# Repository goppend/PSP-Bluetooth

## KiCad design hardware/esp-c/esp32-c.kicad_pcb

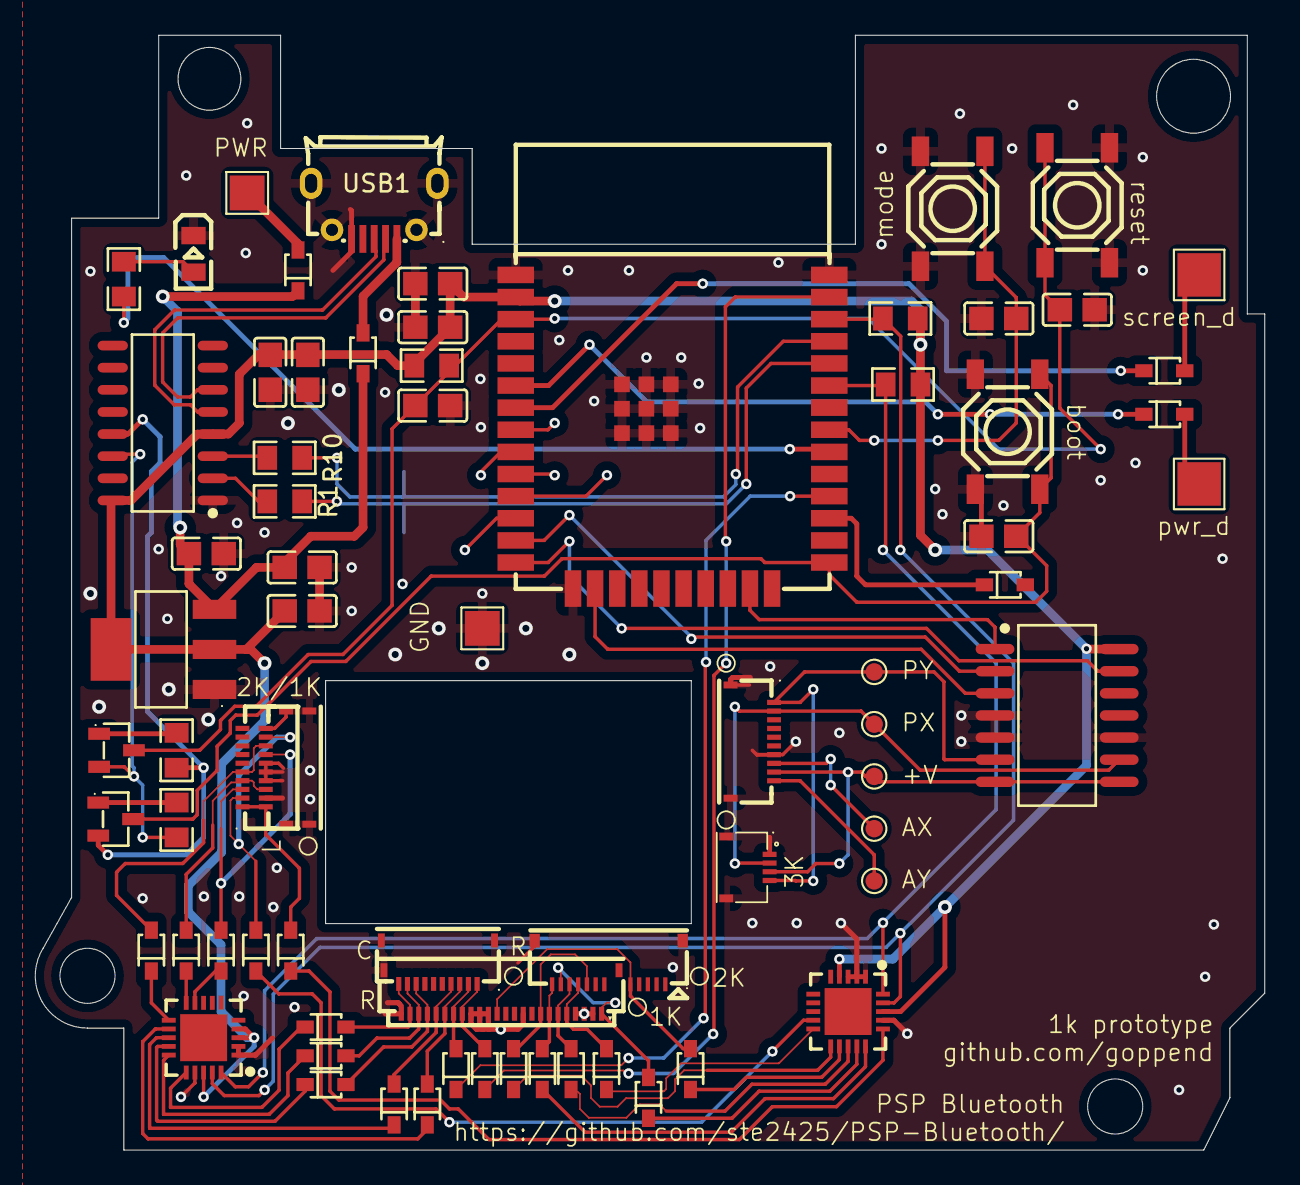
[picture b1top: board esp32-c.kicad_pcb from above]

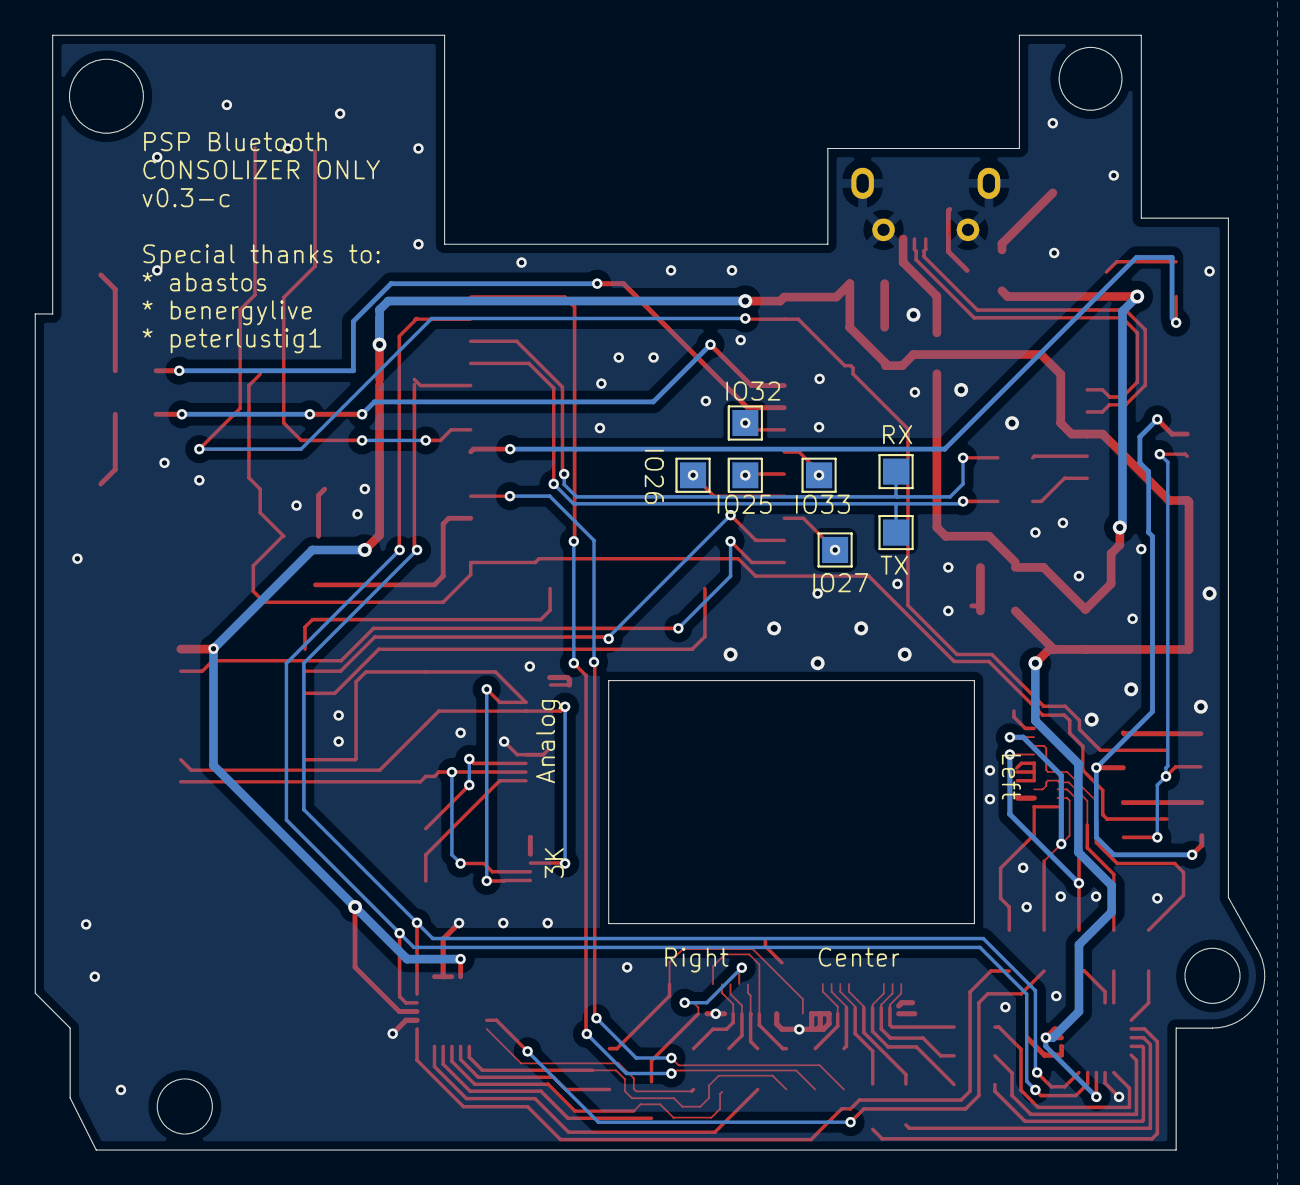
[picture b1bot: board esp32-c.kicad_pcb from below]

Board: 2 copper layers, 70.6 x 64.0 mm, 78 parts (7 on the bottom side), 77 nets.

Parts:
BOOT1: TS-1187A-B-A-B; SW-SMD_4P-L5.1-W5.1-P3.70-LS6.5-TL-2
C1, C11: CL21A226MAQNNNE; C0805
C2, C4, C8, C10, C12: CC0805KRX7R9BB104; C0805
C5: CL21B105KBFNNNE; C0805
C6, C9, C13: CL21A106KAYNNNE; C0805
D1, D2, D3, D4, D5, D6, D7, D8, D9, D10, D11, D12, D13, D20, D21, D22, D23, D24, D25, D26, D27, D28, D29: 1N5819WS; SOD-323_L1.8-W1.3-LS2.5-RD
LED1: FC-2012HRK-620D; LED0805-R-RD
MODE1: TS-1187A-B-A-B; SW-SMD_4P-L5.1-W5.1-P3.70-LS6.5-TL-2
R1, R10: 0805W8F1001T5E; R0805
R2, R3, R7: 0805W8F1002T5E; R0805
R4, R5: 0805W8F4701T5E; R0805
R9: 0805W8F3301T5E; R0805
RESET1: TS-1187A-B-A-B; SW-SMD_4P-L5.1-W5.1-P3.70-LS6.5-TL-2
TP1, TP2, TP3, TP7, TP8: TestPoint; TestPoint_Pad_D1.0mm
TP4, TP17: TestPoint; TestPoint_Pad_2.0x2.0mm
TP5, TP6: TestPoint; TestPoint_Pad_2.5x2.5mm
TP12, TP13, TP14, TP15, TP16, TP35, TP36: TestPoint; TestPoint_Pad_1.5x1.5mm
U1, U4: MCP23008-E/ML; QFN-20_L4.0-W4.0-P0.50-BL-EP2.7
U2: CH340C_C7464026; SOP-16_L10.0-W3.9-P1.27-LS6.0-BL
U3, U8: SS8050_C2150; SOT-23-3_L2.9-W1.3-P1.90-LS2.4-BR
U5: MCP42010T-I/SL; SOIC-14_L10.0-W5.5-P1.27-LS7.8-BL
U6, U6-1k1, U10, U11: HC-FPC-05-09-10RLTAG; FPC-SMD_10P-P0.50_HC-FPC-05-09-10RLTAG
U7: IPFP051A30472R5; FPC-SMD_4P-P0.50_C9900013912
U9: AMS1117-3_3; SOT-223-3_L6.5-W3.4-P2.30-LS7.0-BR
U10-1k1: FPC-SMD_24P-P0.50_HC-FPC-05-09-24RLTAG
U12: ESP32-WROOM-32E(4MB); WIFI-SMD_ESP32-WROOM-32E
U13: AFC42-S14FMA-1H; CONN-SMD_14P-P0.50_L3.1-W9.0
USB1: MICROXNJ; MICRO-USB-SMD_MICROXNJ

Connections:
+3.3V: C5.2, C6.2, C8.2, C11.2, C12.2, R4.2, R5.2, R7.2, U1.4 (RESET), U1.18 (VDD), U2.4 (V3), U2.16 (VCC), U4.3 (A0), U4.4 (RESET), U4.18 (VDD), U5.14 (VDD), U9.2 (VOUT), U9.4 (VOUT), U12.2 (3V3)
+5V: D2.2 (A), TP17.1
/ESP32/ESPPowerDetect: D21.1 (K), U12.6 (IO34)
/ESP32/ESPScreenDetect: D22.1 (K), U12.7 (IO35)
/ESP32/ESP_BOOT: BOOT1.3 (C), BOOT1.4 (D), C10.2, U8.3 (C), U12.25 (IO0)
/ESP32/ESP_EN: C4.2, C13.2, R7.1, RESET1.3 (C), RESET1.4 (D), U3.3 (C), U12.3 (EN)
/ESP32/ESP_MODE: C2.2, MODE1.3 (C), MODE1.4 (D), U12.31 (IO19)
/ESP32/LEDIndicator: R9.2, U12.30 (IO18)
/PSP Pins 2K/+V: TP3.1, U5.7 (PA1), U5.8 (PA0), U7.3, U11.9
/PSP Pins 2K/Analog_x: TP7.1, U11.8
/PSP Pins 2K/Annalog_y: TP8.1, U11.10
/PSP Pins 2K/PSP_x: TP2.1, U5.9 (PW0), U7.2, U11.2
/PSP Pins 2K/PSP_y: TP1.1, U5.6 (PW1), U7.4, U11.1
/USB Serial & Power/USBD+: U2.5 (UD+), USB1.3 (D+)
/USB Serial & Power/USBD-: U2.6 (UD-), USB1.2 (D-)
DTR_PROG: R2.1, U2.13 (DTR#), U8.2 (E)
ESP_I2C_SCL: R5.1, U1.19 (SCL), U4.19 (SCL), U12.36 (IO22)
ESP_I2C_SDA: R4.1, U1.20 (SDA), U4.20 (SDA), U12.33 (IO21)
ESP_SPI_CS: U5.1 (CS#), U12.23 (IO15)
ESP_SPI_MISO: U5.13 (SO), U12.14 (IO12)
ESP_SPI_MOSI: U5.3 (SI), U12.16 (IO13)
ESP_SPI_SCLK: U5.2 (SCK), U12.13 (IO14)
GND: BOOT1.1 (A), BOOT1.2 (B), C1.1, C2.1, C4.1, C5.1, C6.1, C8.1, C9.1, C10.1, C11.1, C12.1, C13.1, LED1.2 (-), MODE1.1 (A), MODE1.2 (B), RESET1.1 (A), RESET1.2 (B), TP4.1, U1.1 (A2), U1.2 (A1), U1.3 (A0), U1.17 (VSS), U2.1 (GND), U4.1 (A2), U4.2 (A1), U4.17 (VSS), U5.4 (VSS), U5.5 (PB1), U5.10 (PB0), U6.11, U6.12, U6-1k1.2, U6-1k1.4, U6-1k1.5, U6-1k1.6, U6-1k1.10, U6-1k1.11, U6-1k1.12, U7.1, U7.5, U7.6, U9.1 (GND), U10.11, U10.12, U10-1k1.2, U10-1k1.3, U10-1k1.4, U10-1k1.10, U10-1k1.14, U10-1k1.15, U10-1k1.16, U10-1k1.24, U10-1k1.25, U11.7, U11.11, U11.12, U12.1 (GND), U12.15 (GND), U12.38 (GND), U12.39 (GND), U13.0, USB1.5 (GND), USB1.6 (SH1), USB1.7 (SH2), USB1.8 (SH3), USB1.9 (SH4)
GPIO_GND: D13.1 (K), U12.27 (IO16)
L1: D24.1 (K), U1.16 (GP7)
unnamed: D1.2 (A), U10.1, U10-1k1.17
unnamed: C1.2, C9.2, D2.1 (K), D23.1 (K), U9.3 (VIN)
unnamed: D3.2 (A), U6.2, U6-1k1.9
unnamed: D4.2 (A), U6.3, U6-1k1.7
unnamed: D5.2 (A), U6.4, U6-1k1.3
unnamed: D6.2 (A), U6.5, U6-1k1.8
unnamed: D7.2 (A), U10-1k1.7, U13.14
unnamed: D8.2 (A), U10-1k1.1, U13.13
unnamed: D9.2 (A), U10-1k1.6, U13.12
unnamed: D10.2 (A), U10-1k1.5, U13.11
unnamed: D11.2 (A), U10-1k1.8, U13.10
unnamed: D12.2 (A), U10-1k1.13, U13.5
unnamed: D20.2 (A), U10.2, U10-1k1.18
unnamed: D21.2 (A), TP5.1
unnamed: D22.2 (A), TP6.1
unnamed: D24.2 (A), U6.1, U6-1k1.1
unnamed: D25.2 (A), U10.3, U10-1k1.19
unnamed: D26.2 (A), U10.4, U10-1k1.20
unnamed: D27.2 (A), U10.8, U10-1k1.21
unnamed: D28.2 (A), U10.9, U10-1k1.22
unnamed: D29.2 (A), U10.10, U10-1k1.23
unnamed: LED1.1 (+), R9.1
unnamed: R10.2, U2.3 (RXD)
unnamed: R1.2, U2.2 (TXD)
unnamed: R2.2, U3.1 (B)
unnamed: R3.2, U8.1 (B)
unnamed: TP14.1, U12.10 (IO25)
unnamed: TP13.1, U12.11 (IO26)
unnamed: TP12.1, U12.12 (IO27)
unnamed: TP16.1, U12.8 (IO32)
unnamed: TP15.1, U12.9 (IO33)
PSP_SELECT: D20.1 (K), U12.28 (IO17)
PSP_START: D1.1 (K), U12.37 (IO23)
RTS_PROG: R3.1, U2.14 (RTS#), U3.2 (E)
UART_RX: R10.1, TP36.1, U12.35 (TXD0)
UART_TX: R1.1, TP35.1, U12.34 (RXD0)
VBUS: D23.2 (A), USB1.1 (VBUS)
circle: D10.1 (K), U1.10 (GP1)
cross: D11.1 (K), U1.11 (GP2)
display: D26.1 (K), U4.13 (GP4)
down: D6.1 (K), U4.11 (GP2)
home: D29.1 (K), U4.16 (GP7)
left: D5.1 (K), U4.10 (GP1)
power: D12.1 (K), U1.12 (GP3)
r1: D8.1 (K), U1.14 (GP5)
right: D3.1 (K), U1.9 (GP0)
sound: D25.1 (K), U4.12 (GP3)
square: D7.1 (K), U1.15 (GP6)
triangle: D9.1 (K), U1.13 (GP4)
up: D4.1 (K), U4.9 (GP0)
voldown: D28.1 (K), U4.15 (GP6)
volup: D27.1 (K), U4.14 (GP5)

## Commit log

2024-12-20 Cleaned up psp pins schematic sheet and added backups and lock files to gitignore file.
2024-12-22 Add right-hand board connector, restructure schematic sheet for button connectors.
2024-12-22 Add 1K board connectors to board layout. Remove some unused pins from U13 footprint.
2024-12-22 Update component R7 to use 0805 package instead of 0402. Tweak some associated traces.
